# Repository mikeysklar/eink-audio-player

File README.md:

# Frisson

A desktop audio player with a quad-colour e-ink screen, four keys and a thumb wheel. It will let you pick a letter to jump straight to an artist, album or song, so you never scroll through a long list.

It plays FLAC files. 16-bit/44.1 kHz works now; the goal is up to 24-bit/96 kHz, higher quality than a CD. Some people get frisson, a chill or goose bumps on the neck, from music they love, and that slightly better fidelity can make it easier to feel.

Site: https://mikeysklar.github.io/frisson/

Docs: [Hardware](docs/HARDWARE.md) · [Design](docs/DESIGN.md) · [Printing](docs/PRINTING.md)

Parts are labelled in the [interactive anatomy page](https://mikeysklar.github.io/frisson/anatomy.html).

## How it works

- An Adafruit Feather RP2350 reads FLAC files from a microSD card on the display's EYESPI breakout, over SPI.
- A TLV320DAC3100 DAC takes I2S from the Feather on A0, A1 and A2, and drives the headphone jack. A jumper wire from TP1 to TP2 feeds it a 15 MHz MCLK from D5; without it the audio sounds muffled.
- The 2.13 inch quad-colour e-ink screen shows the artist and track.
- A NeoKey 1x4 on STEMMA QT gives next, previous, play and artist.
- An ANO rotary encoder on the stand gives the thumb a wheel and five buttons. It chains off the NeoKey over STEMMA QT.
- A 2000 mAh LiPo powers it. A slide switch turns it on and off.

## The board

The four boards plug into one single-sided milled PCB. It has top copper only, 0.4 mm traces, a GND fill with 0.1 mm clearance, and 0805 0R jumpers where traces cross. There are no vias. Two large pads, TP1 and TP2, take a hand-soldered wire from Feather D5 to the TLV320's MCLK.

- `kicad/` has the KiCad project and the 3D models it uses. The ANO is in it too, as a reference part off the board, where the stand puts it.
- `kicad/3d/adafruit-hq/` rebuilds the board models: Adafruit's CAD parts on Adafruit's own boards, with mask, silkscreen and pads.
- `kicad/fab/` has the Gerber and drill files for milling or a board house.
- `kicad/scripts/` has the scripts that generate the board and check the layout plan.

Without the landing pad, the same circuit on a breadboard takes 22 jumper wires:

## Firmware

`firmware/` is a CircuitPython FLAC player with e-ink menus, up to 24-bit / 96 kHz. Browse with the ANO wheel, and play, pause, skip and scan with the NeoKeys. See [firmware/README.md](firmware/README.md) for the jumper, pins, libraries and controls.

## The stand

A minimal "mini arcade" skeleton. The screen tilts back 65 degrees. The keys sit on their own deck in front, at 10 degrees. It is five printed parts held by 12 M2.5 screws into brass heat inserts, so it comes apart and goes back together easily. The red chassis is both cheeks, the feet and the ANO mount in one piece. The ANO sits past the end of the keys, closer to you, for the thumb.

- `enclosure/` has the FreeCAD scripts, STEP and STL files, and `frisson.FCStd`.
- To rebuild the stand, run `freecadcmd enclosure/assemble_arcade.py`.

## Parts

| Part | Adafruit PID |
| --- | --- |
| [Feather RP2350](https://www.adafruit.com/product/6000) | 6000 |
| [TLV320DAC3100 I2S DAC](https://www.adafruit.com/product/6309) | 6309 |
| [2.13 inch quad-colour e-ink display](https://www.adafruit.com/product/6366) | 6366 |
| [EYESPI breakout](https://www.adafruit.com/product/5613) | 5613 |
| [NeoKey 1x4](https://www.adafruit.com/product/4980) | 4980 |
| [LiPo 2000 mAh](https://www.adafruit.com/product/2011) | 2011 |
| [ANO rotary encoder, I2C](https://www.adafruit.com/product/6310) | 6310 |

Full parts list, pin map and screws: [docs/HARDWARE.md](docs/HARDWARE.md).

## Renders

- `blender/` has the scene scripts for the turntable and explode renders. It follows the Metal GPU Cycles recipe.
- `anatomy/` has the sources for the anatomy figure. Rebuilding it needs the [Anatomy kit](https://skills.wheresryan.sh/anatomy).

## Layout

```
README.md
LICENSE
.gitignore
docs/          Pages site, renders, anatomy page and docs
kicad/         KiCad project, 3D models, fab files and generator scripts
enclosure/     FreeCAD sources, STEP and STL files
blender/       render scripts and scenes
anatomy/       anatomy build sources
```

## License

MIT-0 (MIT No Attribution). See [LICENSE](LICENSE).

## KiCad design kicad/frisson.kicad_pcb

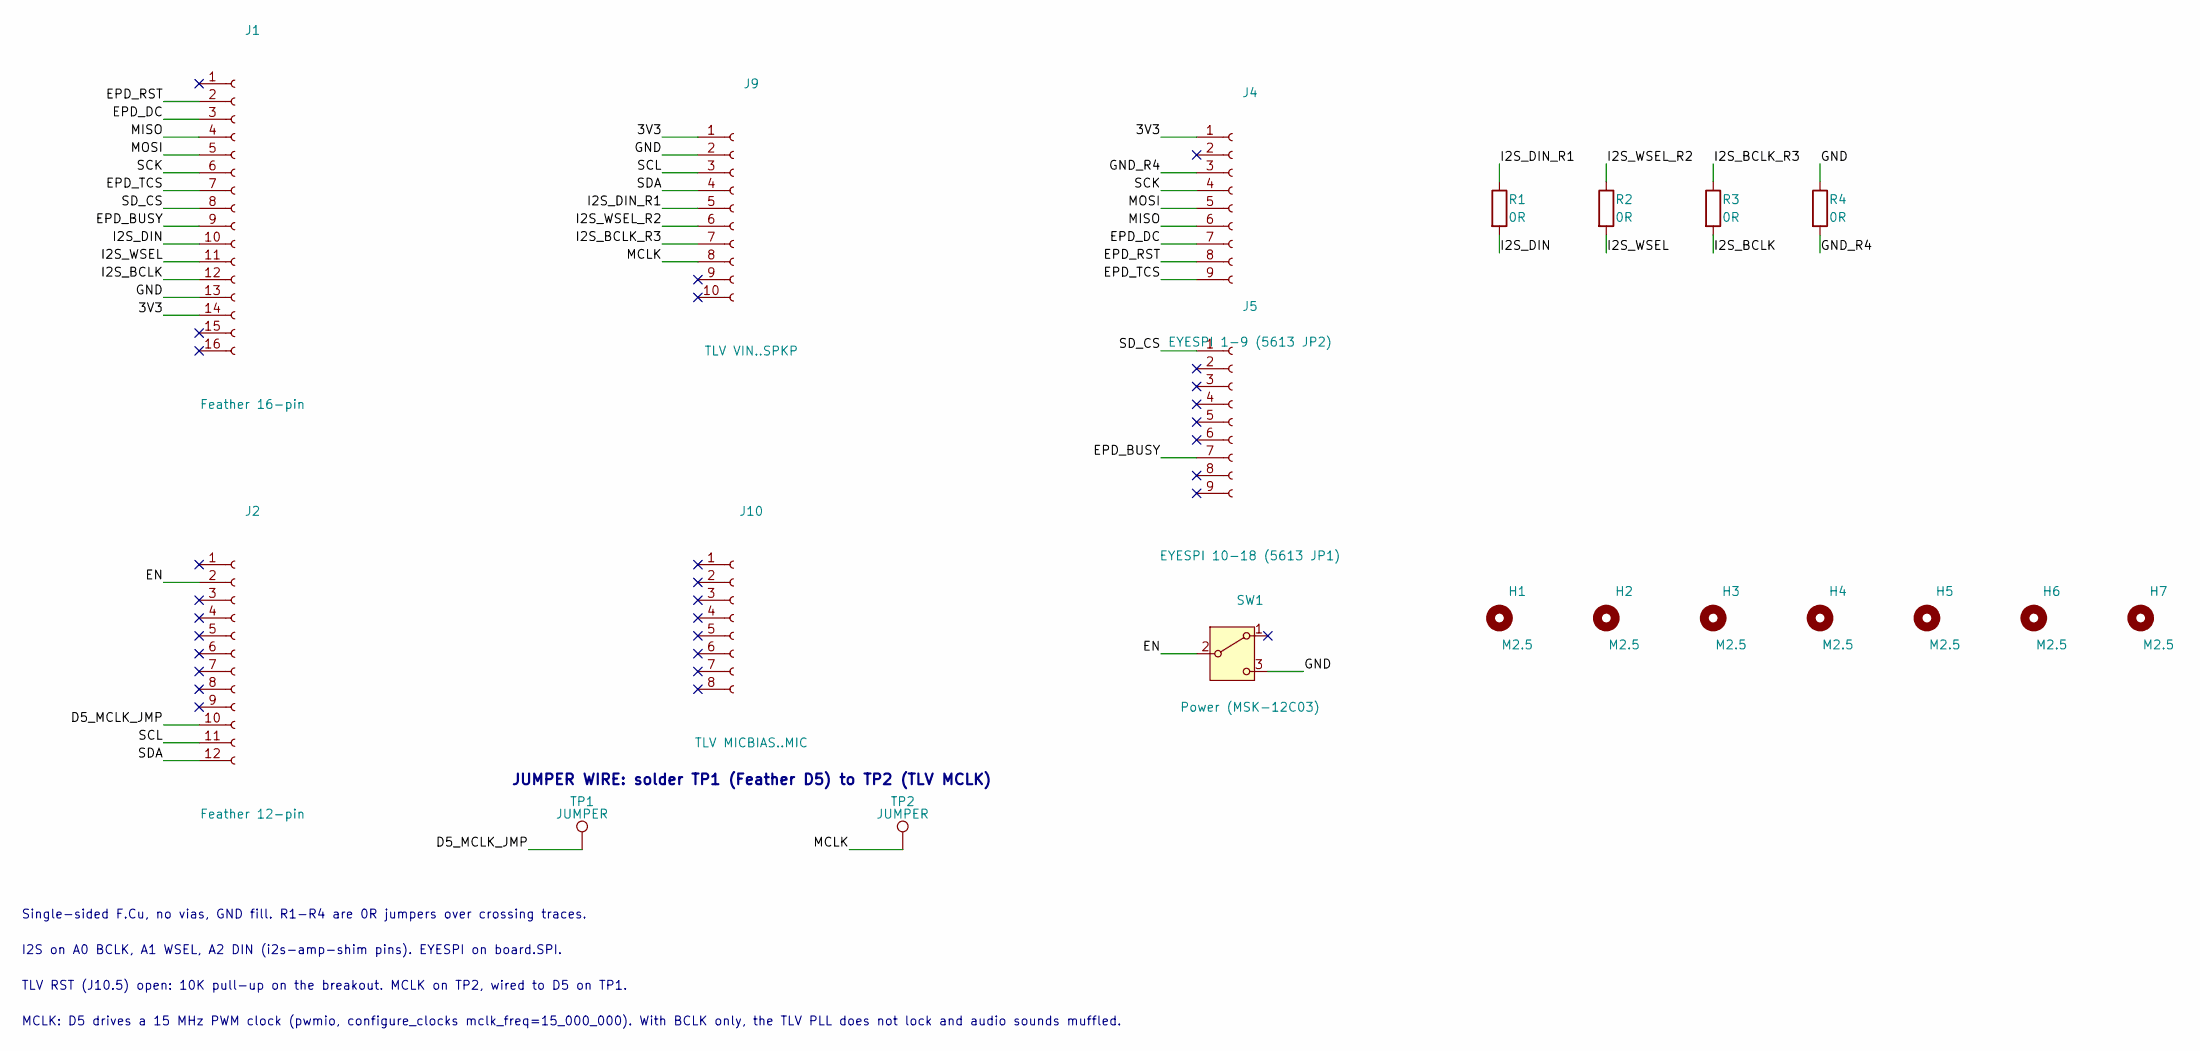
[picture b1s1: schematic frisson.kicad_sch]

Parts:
H1, H2, H3, H4, H5, H6, H7: M2.5; MountingHole_2.7mm
J1: Feather 16-pin; PinSocket_1x16_P2.54mm_Vertical_SMD_Pin1Left
J2: Feather 12-pin; PinSocket_1x12_P2.54mm_Vertical_SMD_Pin1Left
J4: EYESPI 1-9 (5613 JP2); PinSocket_1x09_P2.54mm_Vertical_SMD_Pin1Left
J5: EYESPI 10-18 (5613 JP1); PinSocket_1x09_P2.54mm_Vertical_SMD_Pin1Left
J9: TLV VIN..SPKP; PinSocket_1x10_P2.54mm_Vertical_SMD_Pin1Left
J10: TLV MICBIAS..MIC; PinSocket_1x08_P2.54mm_Vertical_SMD_Pin1Left
R1, R2, R3, R4: 0R; R_0805_2012Metric
SW1: Power (MSK-12C03); SW_SPDT_MSK-12C03
TP1, TP2: JUMPER; JumperPad_3.8x2.0mm

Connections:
/3V3: J1.14, J4.1, J9.1
/D5_MCLK_JMP: J2.10, TP1.1
/EN: J2.2, SW1.2 (B)
/EPD_BUSY: J1.9, J5.7
/EPD_DC: J1.3, J4.7
/EPD_RST: J1.2, J4.8
/EPD_TCS: J1.7, J4.9
/GND: J1.13, J9.2, R4.1, SW1.3 (C)
/GND_R4: J4.3, R4.2
/I2S_BCLK: J1.12, R3.2
/I2S_BCLK_R3: J9.7, R3.1
/I2S_DIN: J1.10, R1.2
/I2S_DIN_R1: J9.5, R1.1
/I2S_WSEL: J1.11, R2.2
/I2S_WSEL_R2: J9.6, R2.1
/MCLK: J9.8, TP2.1
/MISO: J1.4, J4.6
/MOSI: J1.5, J4.5
/SCK: J1.6, J4.4
/SCL: J2.11, J9.3
/SDA: J2.12, J9.4
/SD_CS: J1.8, J5.1

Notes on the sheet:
Single-sided F.Cu, no vias, GND fill. R1-R4 are 0R jumpers over crossing traces.
I2S on A0 BCLK, A1 WSEL, A2 DIN (i2s-amp-shim pins). EYESPI on board.SPI.
TLV RST (J10.5) open: 10K pull-up on the breakout. MCLK on TP2, wired to D5 on TP1.
JUMPER WIRE: solder TP1 (Feather D5) to TP2 (TLV MCLK)
MCLK: D5 drives a 15 MHz PWM clock (pwmio, configure_clocks mclk_freq=15_000_000). With BCLK only, the TLV PLL does not lock and audio sounds muffled.

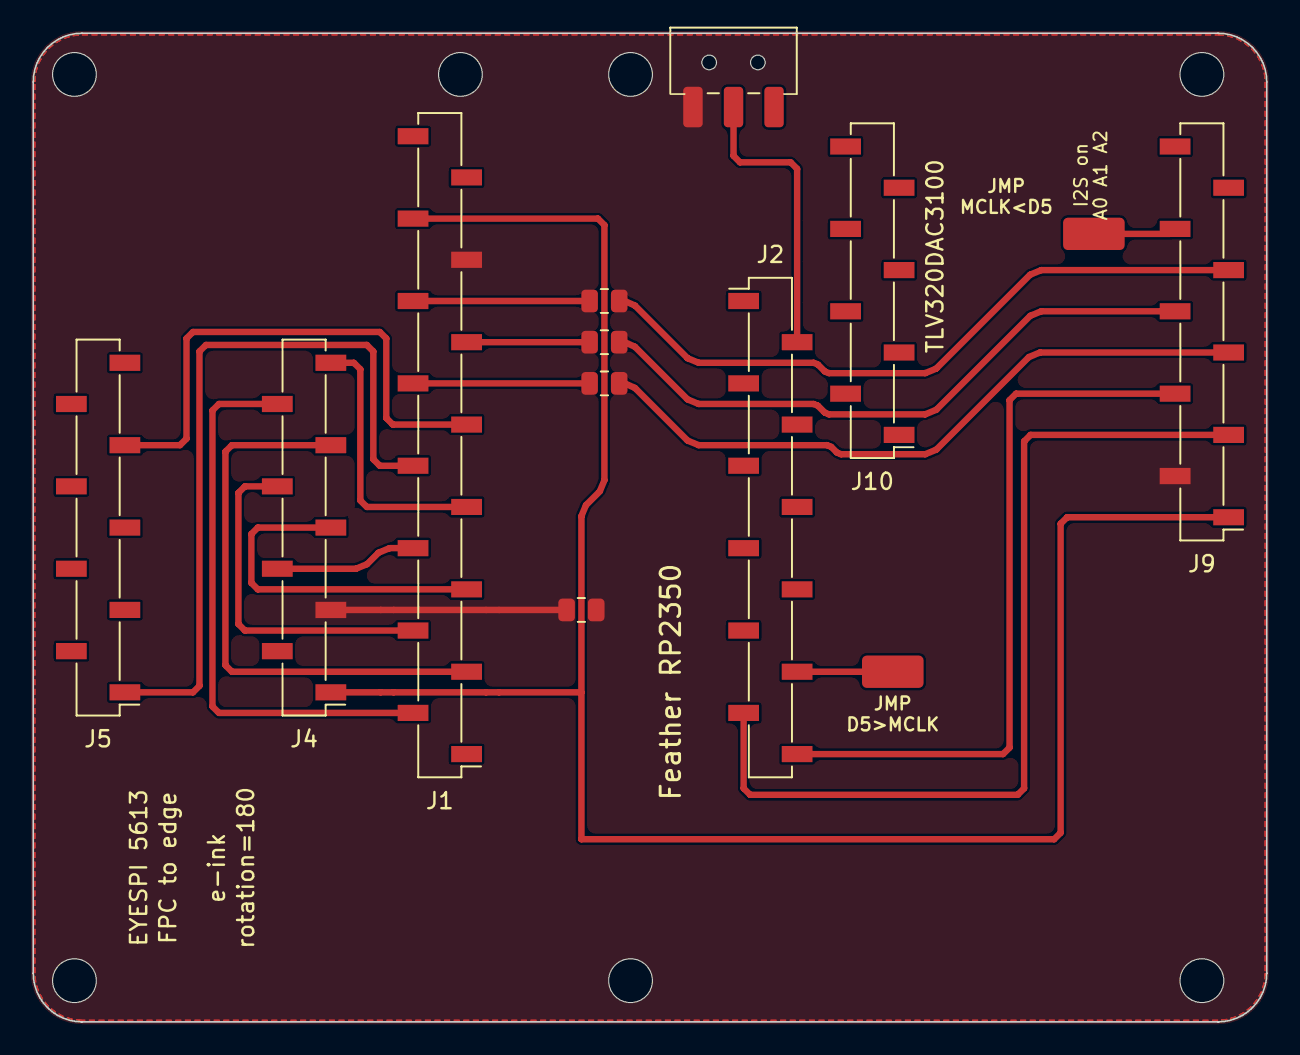
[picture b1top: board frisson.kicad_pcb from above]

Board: 2 copper layers, 76.1 x 61.0 mm, 27 parts (4 on the bottom side), 22 nets.

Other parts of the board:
A1: Feather RP2350 (6000)
A3: TLV320DAC3100 breakout (6309)
A5: NeoKey 1x4 QT (4980), case-mounted
A7: EYESPI breakout (5613)
ANO1: ANO rotary encoder (6310), stand-mounted, referen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
BT1: LiPo 2000 mAh (Adafruit 2011)
DS1: 2.13in quad-colour e-ink (Adafruit 6366)
